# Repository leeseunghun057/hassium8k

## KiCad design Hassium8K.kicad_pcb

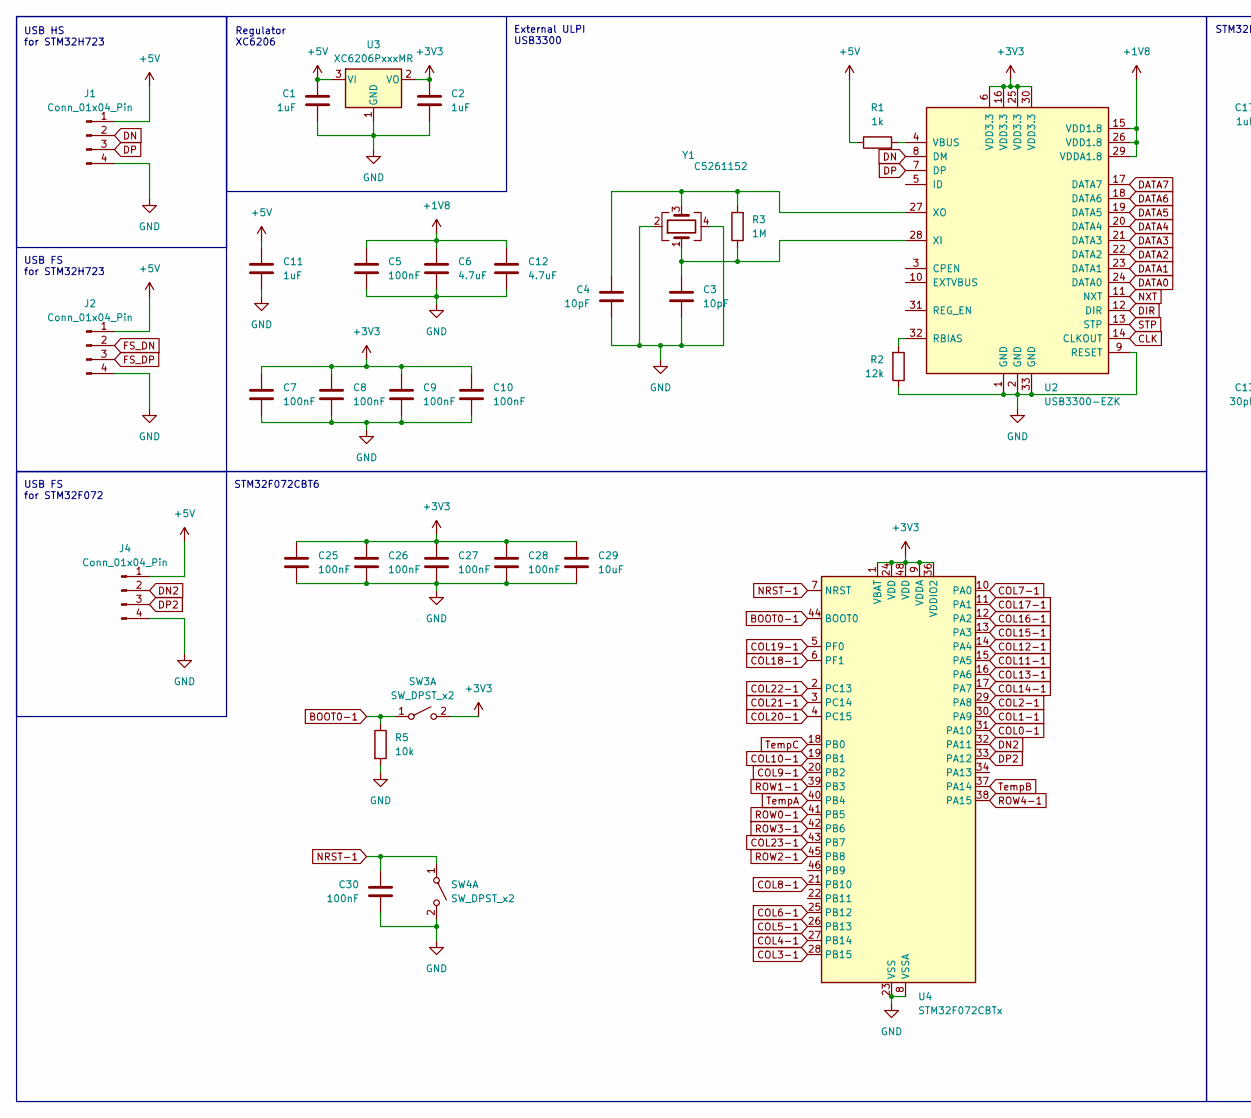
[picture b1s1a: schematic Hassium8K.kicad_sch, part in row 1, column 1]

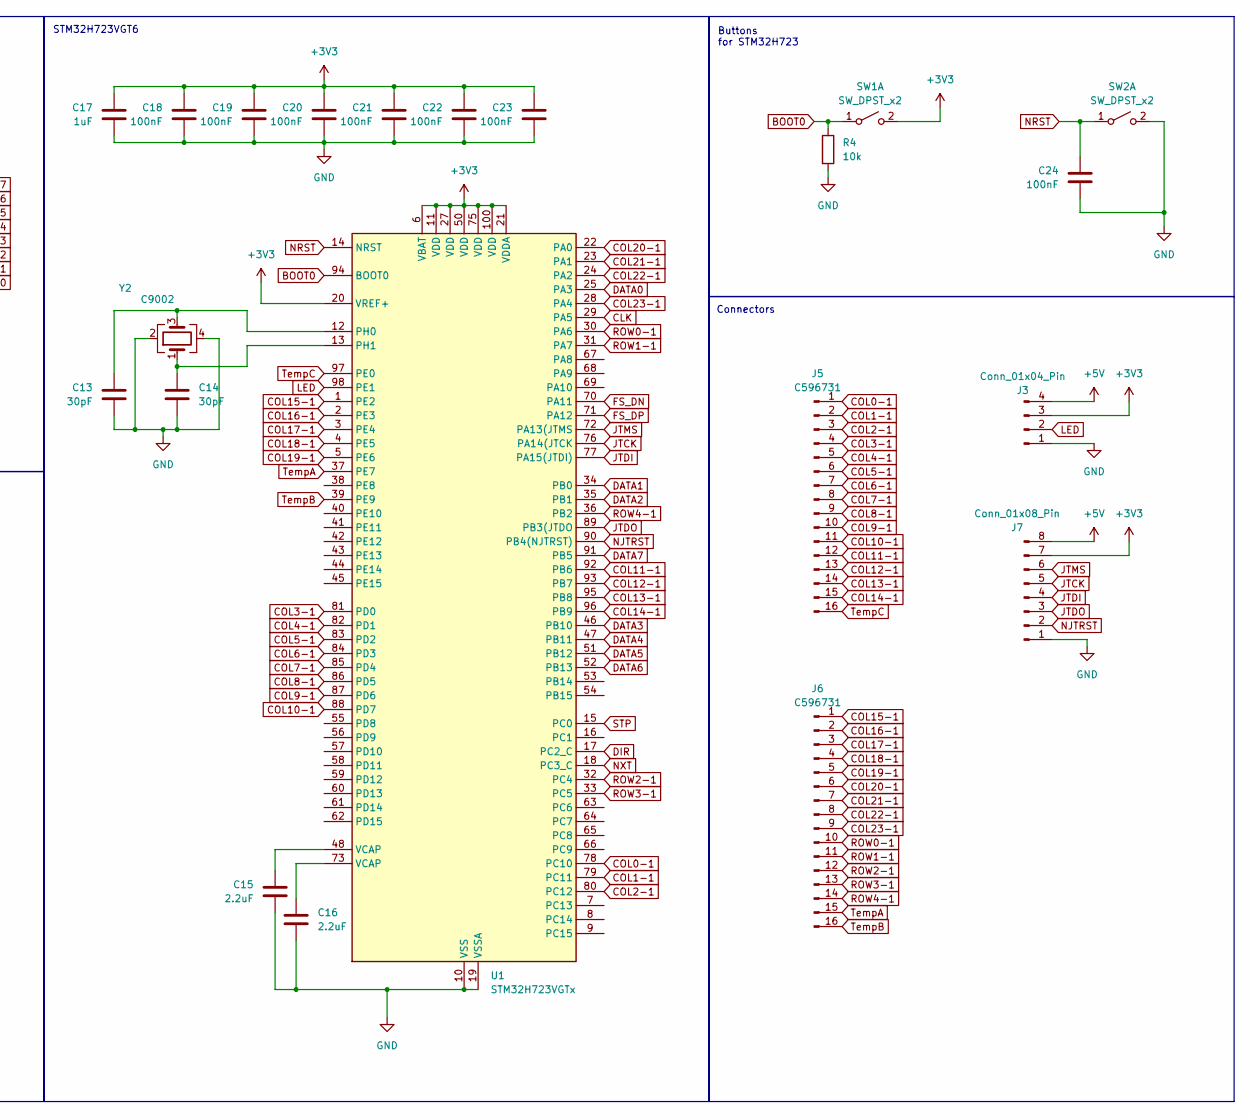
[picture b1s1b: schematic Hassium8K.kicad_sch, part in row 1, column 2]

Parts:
C1, C2, C11, C17: 1uF; C_0402_1005Metric
C3, C4: 10pF; C_0402_1005Metric
C5, C7, C8, C9, C10, C18, C19, C20, C21, C22, C23, C24, C25, C26, C27, C28, C30: 100nF; C_0402_1005Metric
C6, C12: 4.7uF; C_0402_1005Metric
C13, C14: 30pF; C_0402_1005Metric
C15, C16: 2.2uF; C_0402_1005Metric
C29: 10uF; C_0402_1005Metric
J1, J2, J3, J4: Conn_01x04_Pin; JST_SH_SM04B-SRSS-TB_1x04-1MP_P1.00mm_Horizontal
J5, J6: C596731; Hirose_FH12-16S-0.5SH_1x16-1MP_P0.50mm_Horizontal
J7: Conn_01x08_Pin; PinSocket_1x08_P2.54mm_Vertical
R1: 1k; R_0402_1005Metric
R2: 12k; R_0402_1005Metric
R3: 1M; R_0402_1005Metric
R4, R5: 10k; R_0402_1005Metric
SW1, SW2, SW3, SW4: SW_DPST_x2; SW_Push_1P1T_XKB_TS-1187A
U1: STM32H723VGTx; LQFP-100_14x14mm_P0.5mm
U2: USB3300-EZK; QFN-32-1EP_5x5mm_P0.5mm_EP3.45x3.45mm
U3: XC6206PxxxMR; SOT-23-3
U4: STM32F072CBTx; LQFP-48_7x7mm_P0.5mm
Y1: C5261152; Crystal_SMD_3225-4Pin_3.2x2.5mm
Y2: C9002; Crystal_SMD_3225-4Pin_3.2x2.5mm

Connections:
+1V8: C5.1, C6.1, C12.1, U2.15 (VDD1.8), U2.26 (VDD1.8), U2.29 (VDDA1.8)
+3V3: C2.1, C7.1, C8.1, C9.1, C10.1, C17.2, C18.2, C19.2, C20.2, C21.2, C22.2, C23.2, C25.1, C26.1, C27.1, C28.1, C29.1, J3.3, J7.7, SW1.2 (B), SW3.2 (B), U1.6 (VBAT), U1.11 (VDD), U1.20 (VREF+), U1.21 (VDDA), U1.27 (VDD), U1.50 (VDD), U1.75 (VDD), U1.100 (VDD), U2.6 (VDD3.3), U2.16 (VDD3.3), U2.25 (VDD3.3), U2.30 (VDD3.3), U3.2 (VO), U4.1 (VBAT), U4.9 (VDDA), U4.24 (VDD), U4.36 (VDDIO2), U4.48 (VDD)
+5V: C1.1, C11.1, J1.1, J2.1, J3.4, J4.1, J7.8, R1.1, U3.3 (VI)
BOOT0: R4.1, SW1.1 (A), U1.94 (BOOT0)
BOOT0-1: R5.1, SW3.1 (A), U4.44 (BOOT0)
CLK: U1.29 (PA5), U2.14 (CLKOUT)
COL0-1: J5.1, U1.78 (PC10), U4.31 (PA10)
COL1-1: J5.2, U1.79 (PC11), U4.30 (PA9)
COL2-1: J5.3, U1.80 (PC12), U4.29 (PA8)
COL3-1: J5.4, U1.81 (PD0), U4.28 (PB15)
COL4-1: J5.5, U1.82 (PD1), U4.27 (PB14)
COL5-1: J5.6, U1.83 (PD2), U4.26 (PB13)
COL6-1: J5.7, U1.84 (PD3), U4.25 (PB12)
COL7-1: J5.8, U1.85 (PD4), U4.10 (PA0)
COL8-1: J5.9, U1.86 (PD5), U4.21 (PB10)
COL9-1: J5.10, U1.87 (PD6), U4.20 (PB2)
COL10-1: J5.11, U1.88 (PD7), U4.19 (PB1)
COL11-1: J5.12, U1.92 (PB6), U4.15 (PA5)
COL12-1: J5.13, U1.93 (PB7), U4.14 (PA4)
COL13-1: J5.14, U1.95 (PB8), U4.16 (PA6)
COL14-1: J5.15, U1.96 (PB9), U4.17 (PA7)
COL15-1: J6.1, U1.1 (PE2), U4.13 (PA3)
COL16-1: J6.2, U1.2 (PE3), U4.12 (PA2)
COL17-1: J6.3, U1.3 (PE4), U4.11 (PA1)
COL18-1: J6.4, U1.4 (PE5), U4.6 (PF1)
COL19-1: J6.5, U1.5 (PE6), U4.5 (PF0)
COL20-1: J6.6, U1.22 (PA0), U4.4 (PC15)
COL21-1: J6.7, U1.23 (PA1), U4.3 (PC14)
COL22-1: J6.8, U1.24 (PA2), U4.2 (PC13)
COL23-1: J6.9, U1.28 (PA4), U4.43 (PB7)
DATA0: U1.25 (PA3), U2.24 (DATA0)
DATA1: U1.34 (PB0), U2.23 (DATA1)
DATA2: U1.35 (PB1), U2.22 (DATA2)
DATA3: U1.46 (PB10), U2.21 (DATA3)
DATA4: U1.47 (PB11), U2.20 (DATA4)
DATA5: U1.51 (PB12), U2.19 (DATA5)
DATA6: U1.52 (PB13), U2.18 (DATA6)
DATA7: U1.91 (PB5), U2.17 (DATA7)
DIR: U1.17 (PC2_C), U2.12 (DIR)
DN: J1.2, U2.8 (DM)
DN2: J4.2, U4.32 (PA11)
DP: J1.3, U2.7 (DP)
DP2: J4.3, U4.33 (PA12)
FS_DN: J2.2, U1.70 (PA11)
FS_DP: J2.3, U1.71 (PA12)
GND: C1.2, C2.2, C3.2, C4.2, C5.2, C6.2, C7.2, C8.2, C9.2, C10.2, C11.2, C12.2, C13.2, C14.2, C15.1, C16.1, C17.1, C18.1, C19.1, C20.1, C21.1, C22.1, C23.1, C24.1, C25.2, C26.2, C27.2, C28.2, C29.2, C30.2, J1.4, J2.4, J3.1, J4.4, J7.1, R2.1, R4.2, R5.2, SW2.2 (B), SW4.2 (B), U1.10 (VSS), U1.19 (VSSA), U1.26 (VSS), U1.49 (VSS), U1.74 (VSS), U1.99 (VSS), U2.1 (GND), U2.2 (GND), U2.9 (RESET), U2.33 (GND), U3.1 (GND), U4.8 (VSSA), U4.23 (VSS), U4.35 (VSS), U4.47 (VSS), Y1.2, Y1.4, Y2.2, Y2.4
JTCK: J7.5, U1.76 (PA14(JTCK)
JTDI: J7.4, U1.77 (PA15(JTDI))
JTDO: J7.3, U1.89 (PB3(JTDO)
JTMS: J7.6, U1.72 (PA13(JTMS)
LED: J3.2, U1.98 (PE1)
NJTRST: J7.2, U1.90 (PB4(NJTRST))
NRST: C24.2, SW2.1 (A), U1.14 (NRST)
NRST-1: C30.1, SW4.1 (A), U4.7 (NRST)
NXT: U1.18 (PC3_C), U2.11 (NXT)
unnamed: C15.2, U1.48 (VCAP)
unnamed: C16.2, U1.73 (VCAP)
unnamed: C13.1, U1.12 (PH0), Y2.3
unnamed: C14.1, U1.13 (PH1), Y2.1
unnamed: R2.2, U2.32 (RBIAS)
unnamed: R1.2, U2.4 (VBUS)
unnamed: C3.1, R3.1, U2.28 (XI), Y1.1
unnamed: C4.1, R3.2, U2.27 (XO), Y1.3
ROW0-1: J6.10, U1.30 (PA6), U4.41 (PB5)
ROW1-1: J6.11, U1.31 (PA7), U4.39 (PB3)
ROW2-1: J6.12, U1.32 (PC4), U4.45 (PB8)
ROW3-1: J6.13, U1.33 (PC5), U4.42 (PB6)
ROW4-1: J6.14, U1.36 (PB2), U4.38 (PA15)
STP: U1.15 (PC0), U2.13 (STP)
TempA: J6.15, U1.37 (PE7), U4.40 (PB4)
TempB: J6.16, U1.39 (PE9), U4.37 (PA14)
TempC: J5.16, U1.97 (PE0), U4.18 (PB0)

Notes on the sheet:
External ULPI USB3300
Buttons for STM32H723
Regulator XC6206
STM32F072CBT6
USB FS for STM32F072
USB HS for STM32H723
STM32H723VGT6
USB FS for STM32H723
Connectors

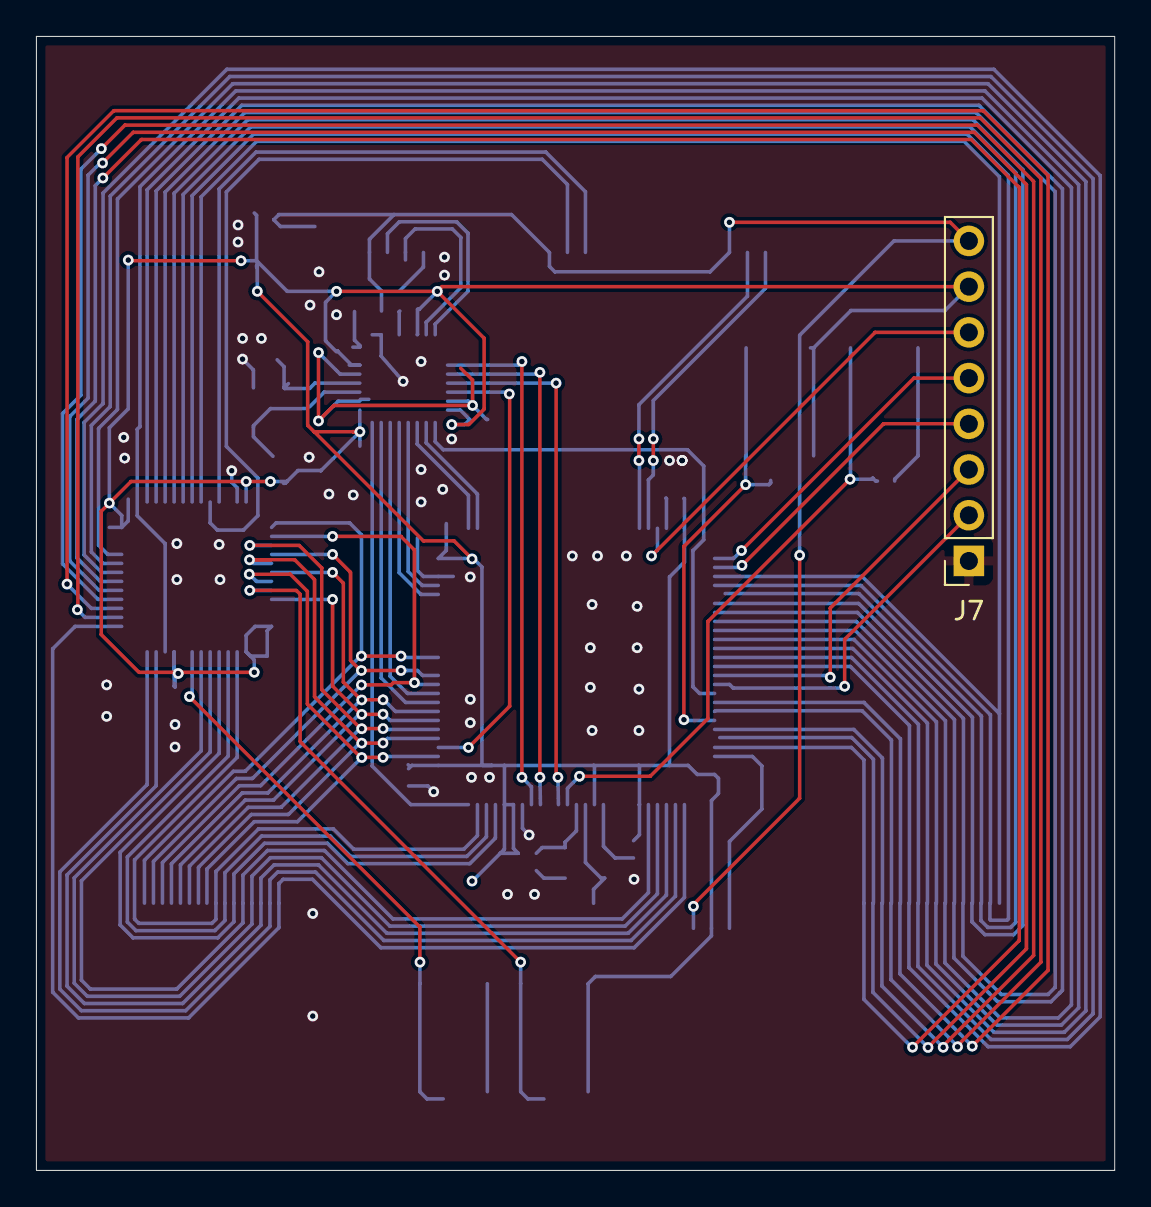
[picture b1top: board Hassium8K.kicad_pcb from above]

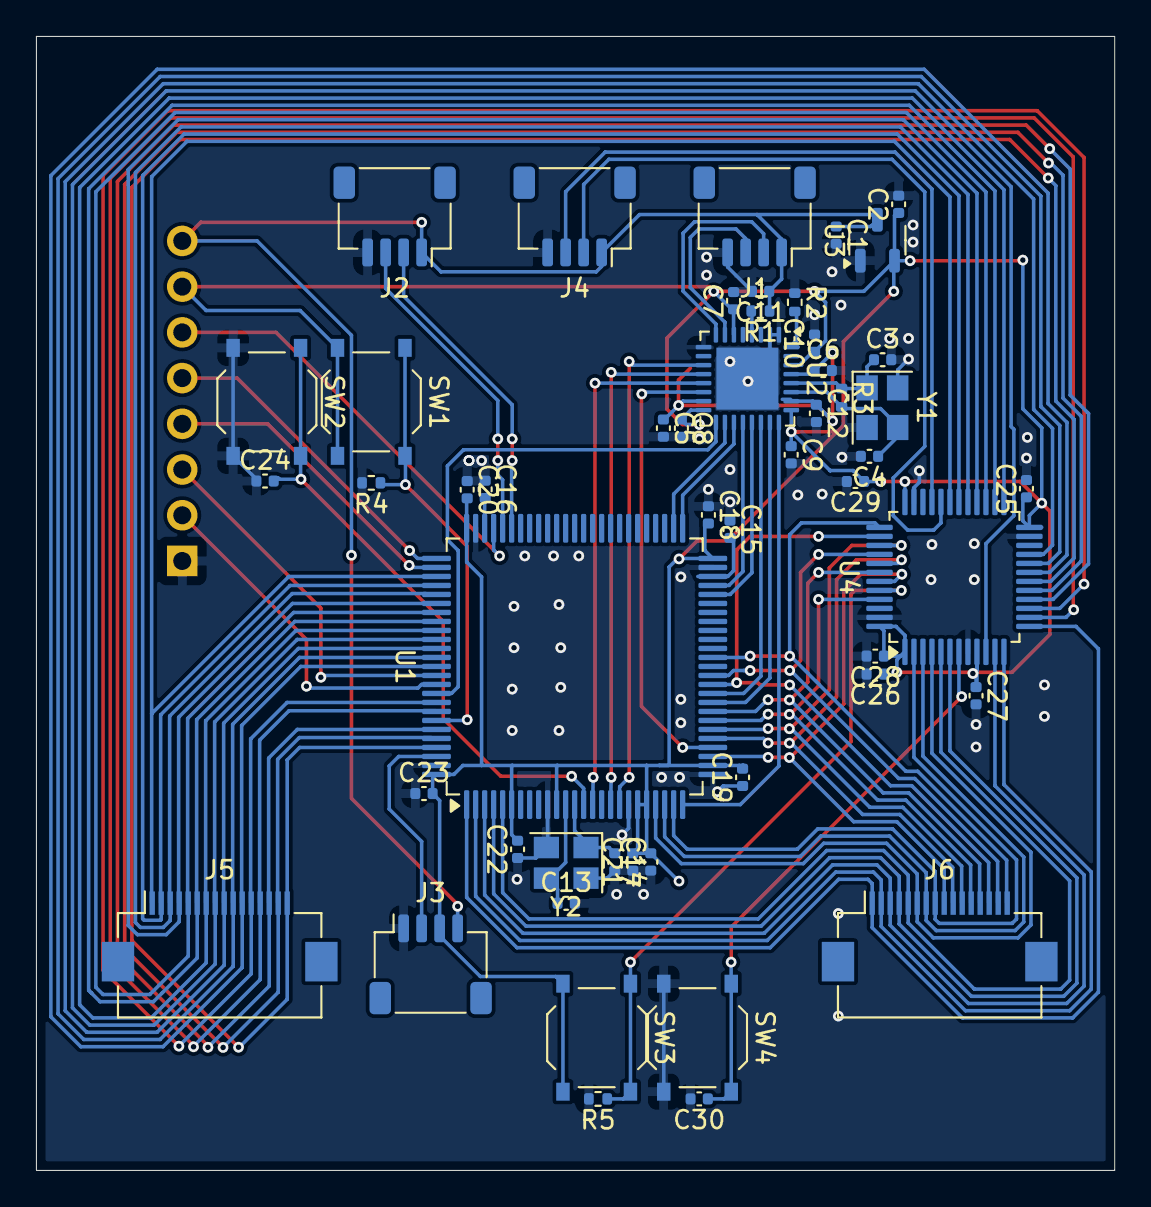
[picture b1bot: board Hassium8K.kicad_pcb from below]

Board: 2 copper layers, 59.9 x 63.0 mm, 52 parts (51 on the bottom side), 72 nets.
